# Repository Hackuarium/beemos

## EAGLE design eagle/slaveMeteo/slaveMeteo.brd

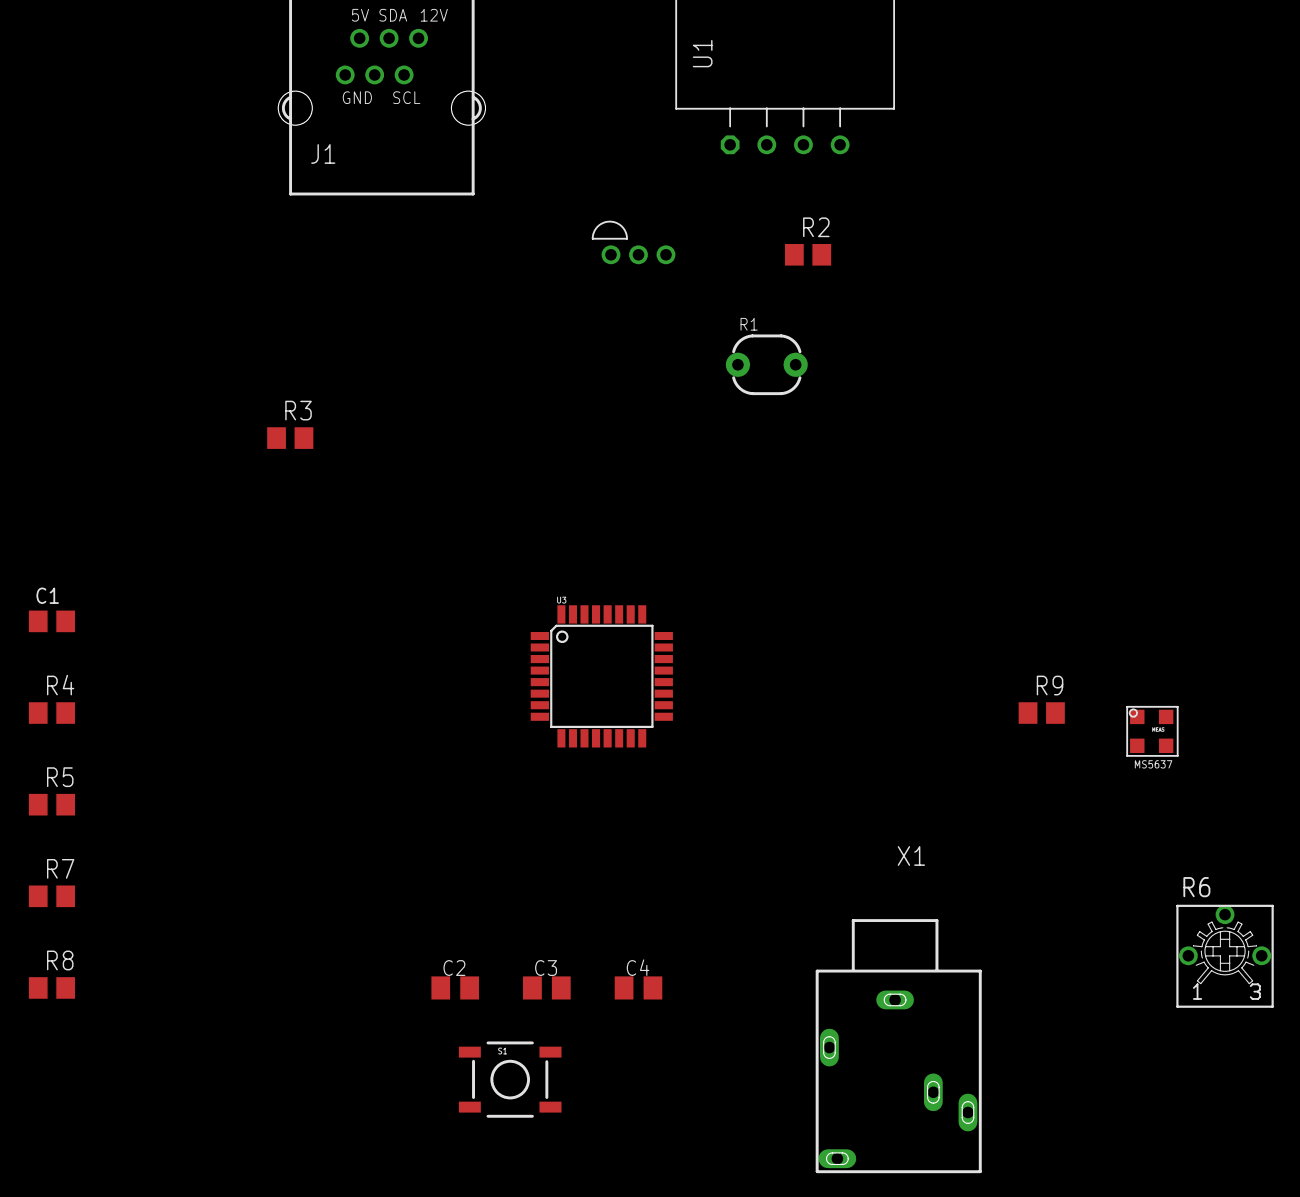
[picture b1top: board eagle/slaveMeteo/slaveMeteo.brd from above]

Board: 2 copper layers, 20 parts (0 on the bottom side), 14 nets, no tracks yet.

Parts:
C1: 100nF; C805
C2, C3, C4: 100nF; C0805K
J1: RJ12RIGHTANGLE-I2C; RJ12-RIGHTANGLE-I2C
R1: PHOTOCELLPTH; PHOTOCELL
R2, R3, R5, R7: R0805
R4, R8: 100k; R0805
R6: 10k; TRIMMER_3362P
R9: 10k; R0805
S1: Reset; TACTILE-SWITCH-SMD-ALT01
U1: RHT03_DHT-22/RA
U3: ATMEGA328; TQFP32-08
U$1: DS1820TO92; DS1820
U$19: MS5637
X1: 1503_09

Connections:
+5V: R1.1, R3.2, R4.2, U1.VDD, U$1.VDD
A0: R3.1, U3.23, U$1.DQ
A1: R1.2, R2.1, U3.24
A2: U1.DATA, U3.25
A6: J1.GND2, U3.19
AREF: C3.1, U3.20
GND: C3.2, C4.2, J1.GND1, R2.2, S1.1, S1.2, U1.GND, U3.3, U3.5, U3.21, U$1.GND, U$19.GND
GND2: R8.1, X1.3
unnamed: C1.1, R4.1, R8.2
unnamed: C1.2, X1.1
RESET: C2.2, R9.1, S1.3, S1.4, U3.29
SCL: J1.SCL, U3.28, U$19.SCL
SDA: J1.SDA, U3.27, U$19.SDA
VCC: C4.1, R9.2, U3.4, U3.6, U3.18, U$19.VDD

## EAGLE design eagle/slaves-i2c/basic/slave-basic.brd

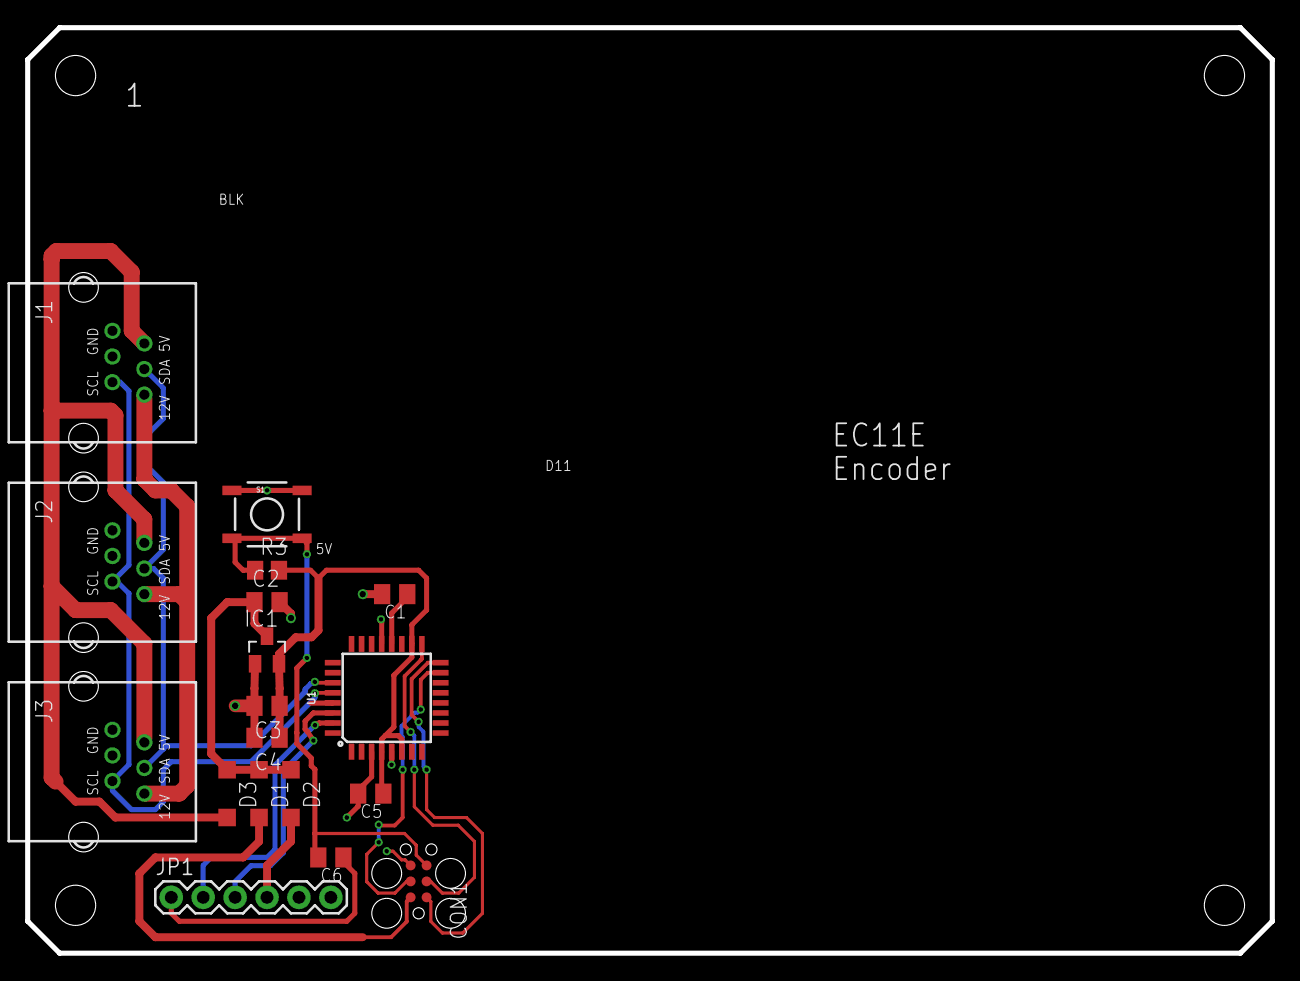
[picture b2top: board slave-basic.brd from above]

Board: 2 copper layers, 99.1 x 73.7 mm, 18 parts (0 on the bottom side), 17 nets.

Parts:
C1, C4, C5, C6: 100nF; C0805K
C2, C3: 10u; C0805K
CON1: SPI; TC2030-MCP
D1, D2, D3: Schottky; SOD123
IC1: MCP1703CB; SOT23
J1, J2, J3: RJ12RIGHTANGLE-I2C; RJ12-RIGHTANGLE-I2C
JP1: FTDI Basic; 1X06
R3: 10k; R0805
S1: Reset; TACTILE-SWITCH-SMD-ALT01
U1: ATMEGA328P_TQFP; TQFP32-08

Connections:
+5V: D3.A, J1.+5V, J2.+5V, J3.+5V
+12V: J1.+12V, J2.+12V, J3.+12V
+XV: C2.1, D1.C, D2.C, D3.C, IC1.3
AREF: C1.1, U1.20
DTR: C6.1, JP1.1
EXT-FTDI: D2.A, JP1.4
EXT-VCC: CON1.5V, D1.A
GND: C1.2, C2.2, C3.2, C4.2, C5.2, CON1.GND, IC1.1, J1.GND1, J1.GND2, J2.GND1, J2.GND2, J3.GND1, J3.GND2, JP1.5, JP1.6, S1.1, S1.2, U1.3, U1.5, U1.21
MISO: CON1.MISO, U1.16
MOSI: CON1.MOSI, U1.15
RESET: C6.2, CON1.RESET, R3.1, S1.3, S1.4, U1.29
RX: JP1.3, U1.30
SCK: CON1.SCK, U1.17
SCL: J1.SCL, J2.SCL, J3.SCL, U1.28
SDA: J1.SDA, J2.SDA, J3.SDA, U1.27
TX: JP1.2, U1.31
VCC: C3.1, C4.1, C5.1, IC1.2, R3.2, U1.4, U1.6, U1.18

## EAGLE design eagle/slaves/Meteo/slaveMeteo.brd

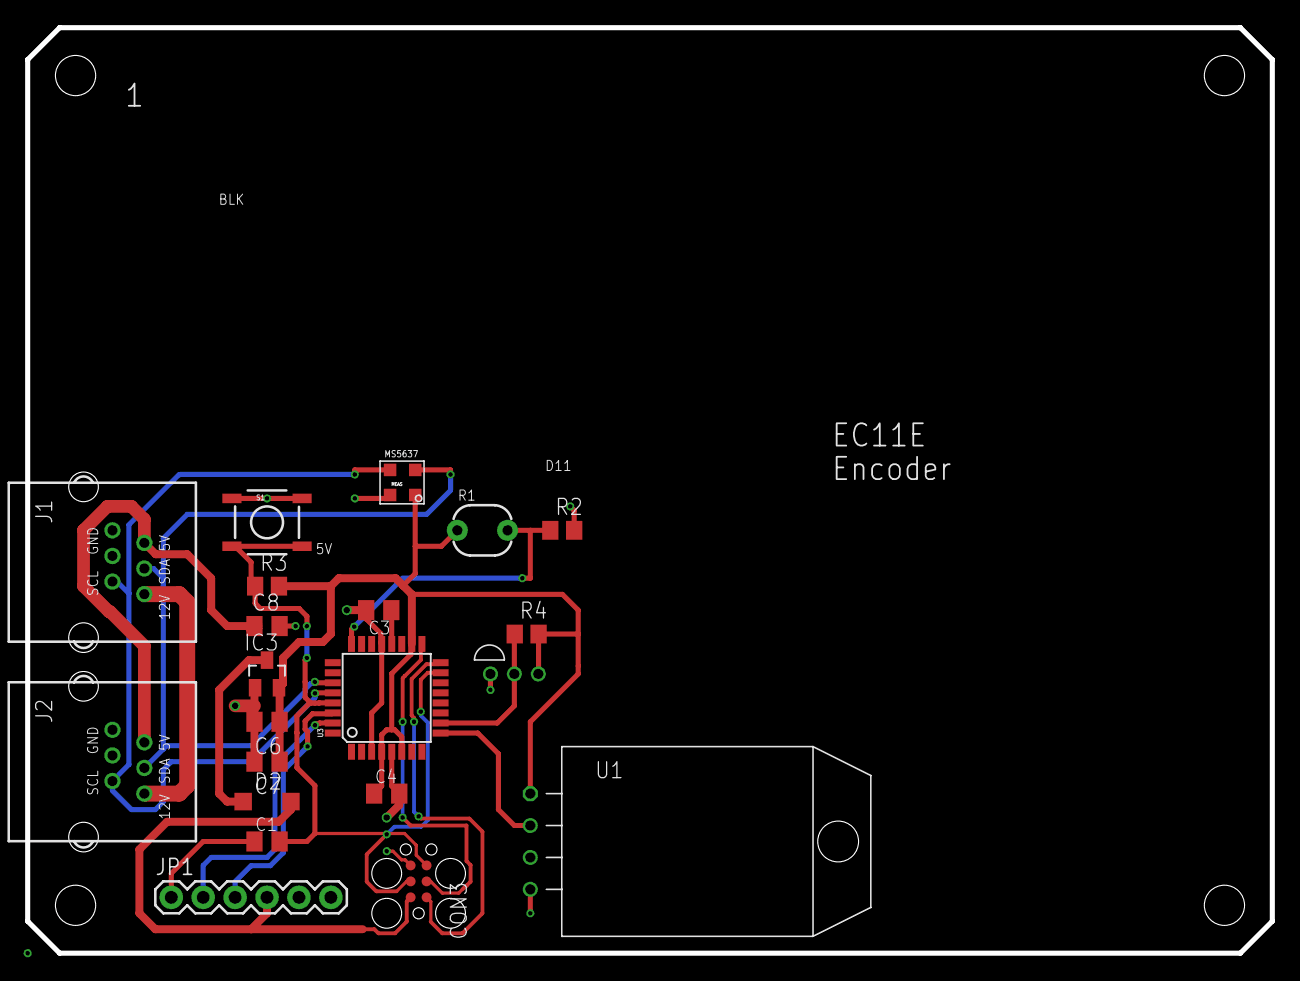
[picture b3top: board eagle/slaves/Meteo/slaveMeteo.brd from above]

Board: 2 copper layers, 99.1 x 73.7 mm, 21 parts (0 on the bottom side), 18 nets.

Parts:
C1, C3, C4, C7: 100nF; C0805K
C6, C8: 10u; C0805K
CON3: SPI; TC2030-MCP
D2: Schottky; SOD123
IC3: MCP1703CB; SOT23
J1, J2: RJ12RIGHTANGLE-I2C; RJ12-RIGHTANGLE-I2C
JP1: FTDI Basic; 1X06
R1: PHOTOCELLPTH; PHOTOCELL
R2, R4: R0805
R3: 10k; R0805
S1: Reset; TACTILE-SWITCH-SMD-ALT01
U1: RHT03_DHT-22/RA
U3: ATMEGA328; TQFP32-08
U$1: DS1820TO92; DS1820
U$19: MS5637

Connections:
+5V: C8.1, D2.C, IC3.3, J1.+5V, J2.+5V
+12V: J1.+12V, J2.+12V
A1: R1.2, R2.1, U3.24
AREF: C3.1, U3.20
D5: U1.DATA, U3.9
D6: R4.1, U3.10, U$1.DQ
DTR: C1.1, JP1.1
EXT-VCC: CON3.5V, D2.A, JP1.4
GND: C3.2, C4.2, C6.2, C7.2, C8.2, CON3.GND, IC3.1, J1.GND1, J1.GND2, J2.GND1, J2.GND2, JP1.5, JP1.6, R2.2, S1.1, S1.2, U1.GND, U3.3, U3.5, U3.21, U$1.GND, U$19.GND
MISO: CON3.MISO, U3.16
MOSI: CON3.MOSI, U3.15
RESET: C1.2, CON3.RESET, R3.1, S1.3, S1.4, U3.29
RX: JP1.3, U3.30
SCK: CON3.SCK, U3.17
SCL: J1.SCL, J2.SCL, U3.28, U$19.SCL
SDA: J1.SDA, J2.SDA, U3.27, U$19.SDA
TX: JP1.2, U3.31
VCC: C4.1, C6.1, C7.1, IC3.2, R1.1, R3.2, R4.2, U1.VDD, U3.4, U3.6, U3.18, U$1.VDD, U$19.VDD

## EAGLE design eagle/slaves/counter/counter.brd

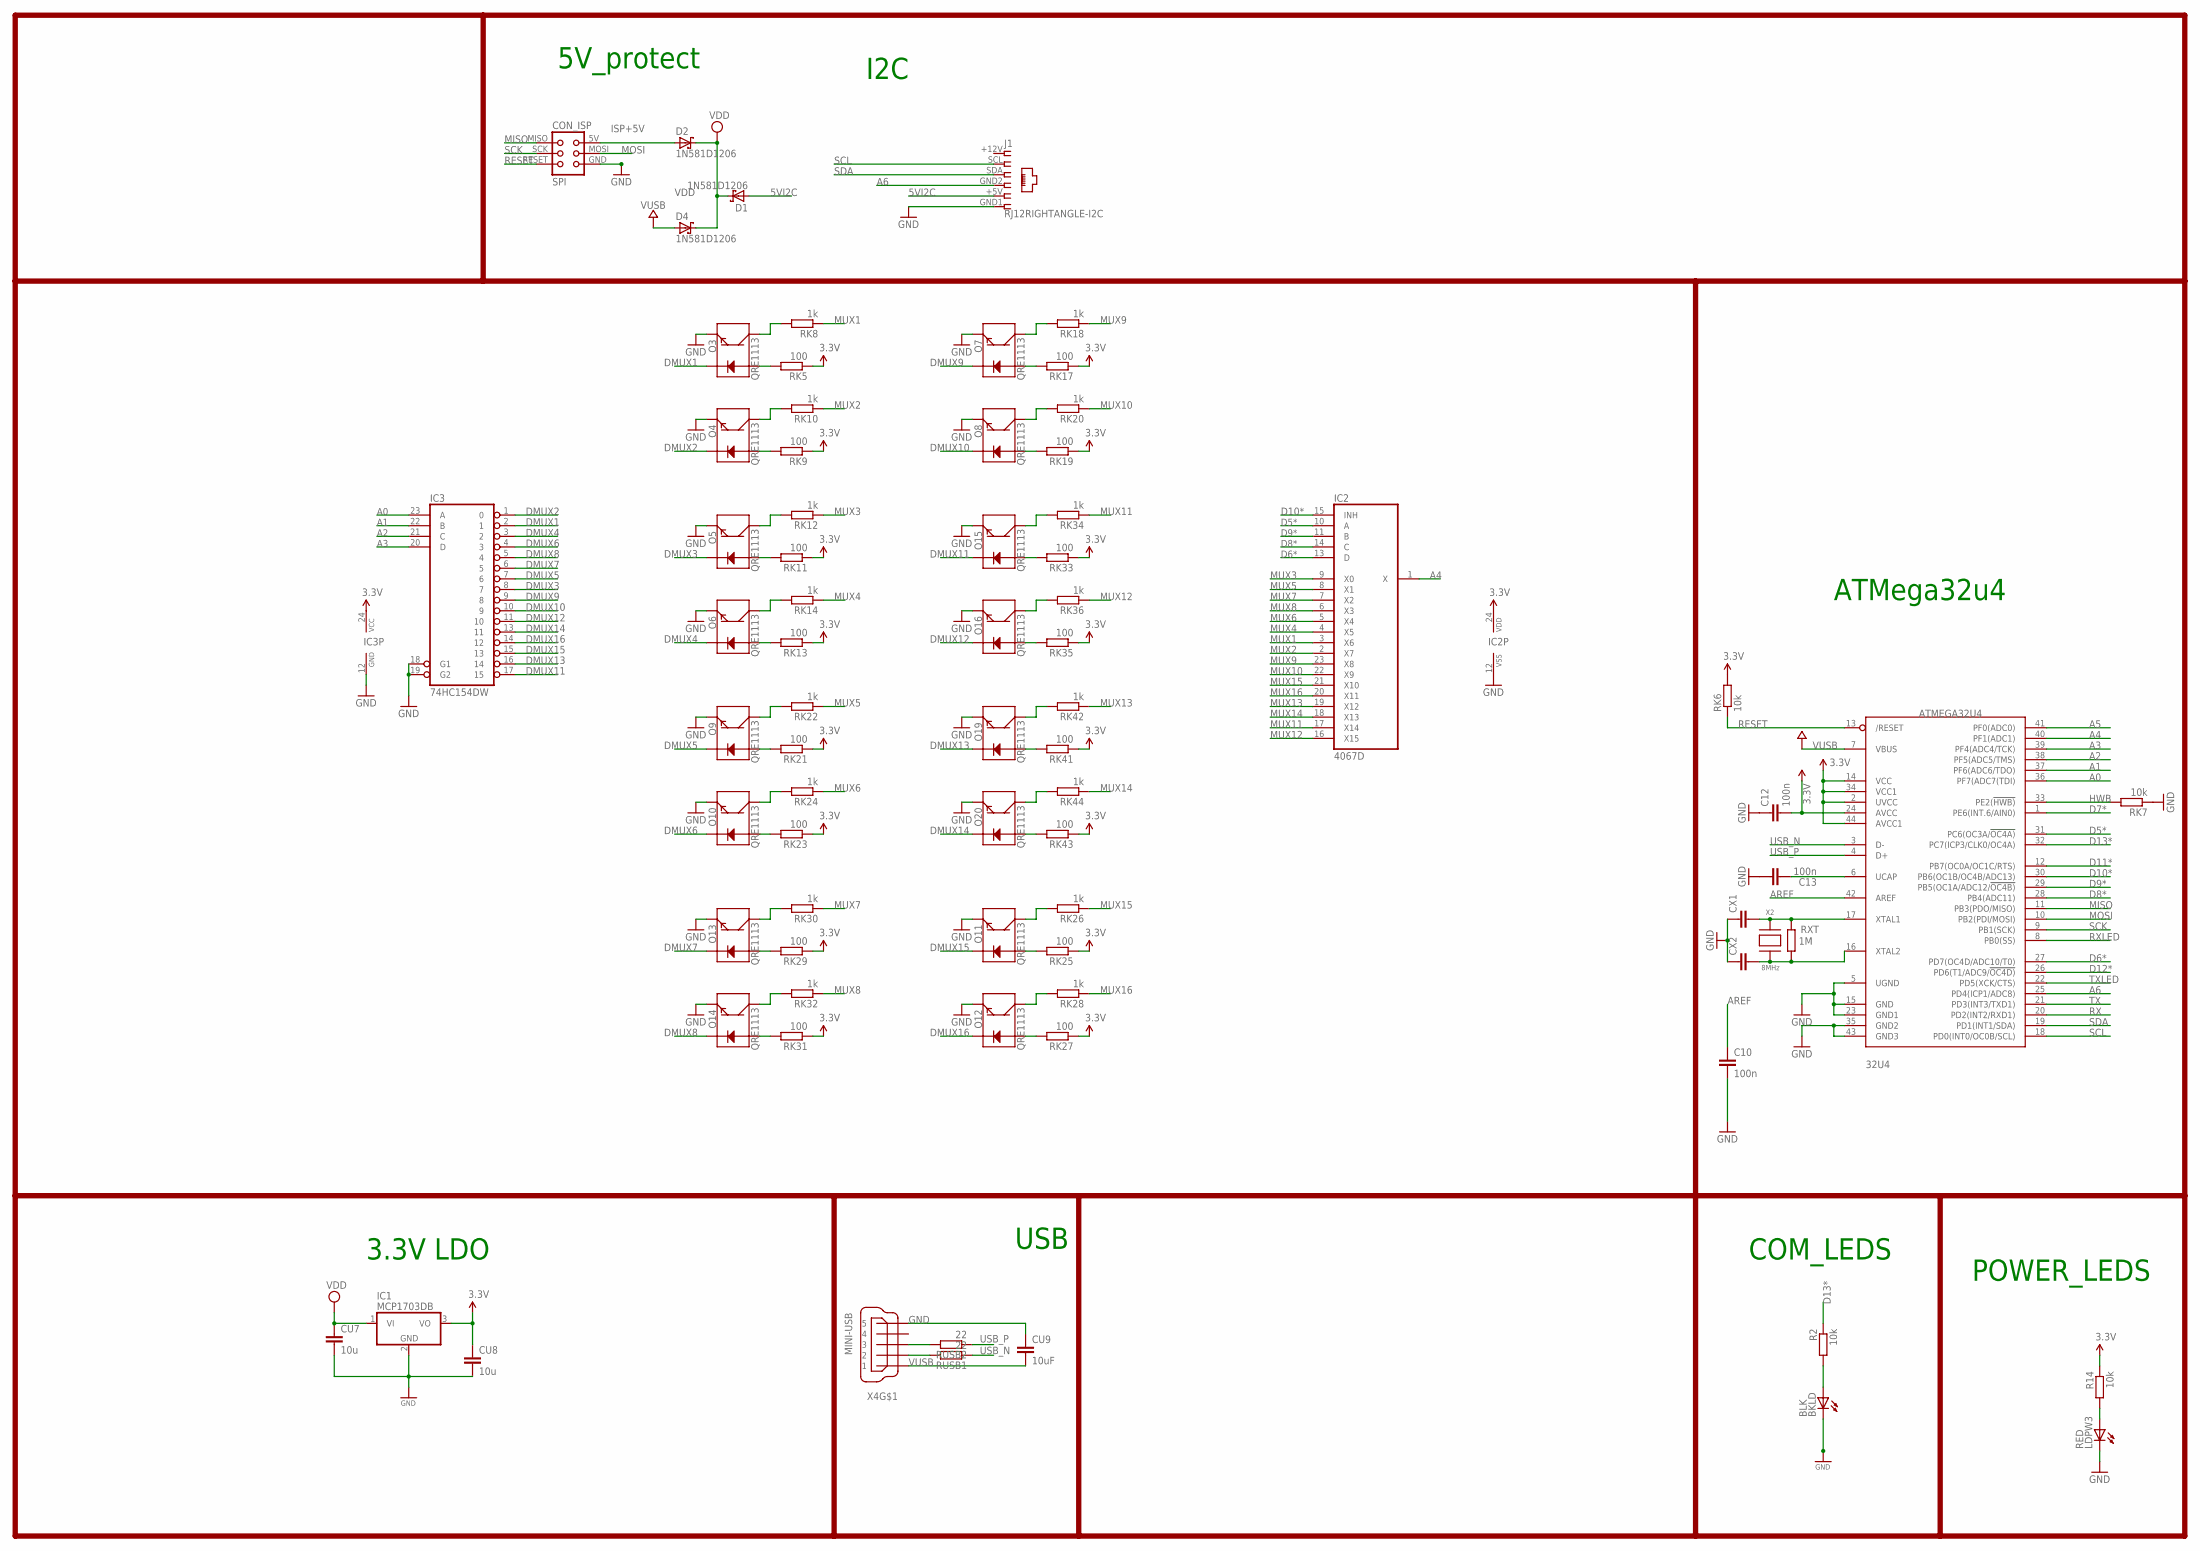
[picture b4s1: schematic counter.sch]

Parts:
32U4: ATMEGA32U4; TQFP44
BKLD: BLK; CHIP-LED0805
C10, C12, C13: 100n; C0805
CON_ISP: SPI; TC2030-MCP-NL
CU7, CU8: 10u; C0805
CU9: 10uF; C0805
CX1, CX2: 22pF; C0805
D1, D2, D4: 1N581D1206; LED-1206
IC1: MCP1703DB; SOT223
IC2: 4067D; SO24W
IC3: 74HC154DW; SO24W
J1: RJ12RIGHTANGLE-I2C; RJ12-RIGHTANGLE-I2C
LDPW3: RED; CHIP-LED0805
O3, O4, O5, O6, O7, O8, O9, O10, O11, O12, O13, O14, O15, O16, O19, O20: QRE1113
R2, R14: 10k; R0805
RK5, RK9, RK11, RK13, RK17, RK19, RK21, RK23, RK25, RK27, RK29, RK31, RK33, RK35, RK41, RK43: 100; M0805
RK6, RK7: 10k; M0805
RK8, RK10, RK12, RK14, RK18, RK20, RK22, RK24, RK26, RK28, RK30, RK32, RK34, RK36, RK42, RK44: 1k; M0805
RUSB1, RUSB2: 22; M0805
RXT: 1M; R0805
X2: 8MHz; NX6035
X4: MINI-USB; 32005-201

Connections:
1: J1.+12V (1)
3.3V: 32U4.2 (UVCC), 32U4.14 (VCC), 32U4.24 (AVCC), 32U4.34 (VCC1), 32U4.44 (AVCC1), C12.2, CU8.1, IC1.3 (VO), IC2.24 (VDD), IC3.24 (VCC), R14.1, RK5.1, RK6.2, RK9.1, RK11.1, RK13.1, RK17.1, RK19.1, RK21.1, RK23.1, RK25.1, RK27.1, RK29.1, RK31.1, RK33.1, RK35.1, RK41.1, RK43.1
5VI2C: D1.A, J1.+5V (5)
A0: 32U4.36 (PF7(ADC7(TDI)), IC3.23 (A)
A1: 32U4.37 (PF6(ADC6/TDO)), IC3.22 (B)
A2: 32U4.38 (PF5(ADC5/TMS)), IC3.21 (C)
A3: 32U4.39 (PF4(ADC4/TCK)), IC3.20 (D)
A4: 32U4.40 (PF1(ADC1)), IC2.1 (X)
A5: 32U4.41 (PF0(ADC0))
A6: 32U4.25 (PD4(ICP1/ADC8)), J1.GND2 (4)
AREF: 32U4.42 (AREF), C10.1
D5*: 32U4.31 (PC6(OC3A/!OC4A)), IC2.10 (A)
D6*: 32U4.27 (PD7(OC4D/ADC10/T0)), IC2.13 (D)
D7*: 32U4.1 (PE6(INT.6/AIN0))
D8*: 32U4.28 (PB4(ADC11)), IC2.14 (C)
D9*: 32U4.29 (PB5(OC1A/ADC12/!OC4B)), IC2.11 (B)
D10*: 32U4.30 (PB6(OC1B/OC4B/ADC13)), IC2.15 (INH)
D11*: 32U4.12 (PB7(OC0A/OC1C/RTS))
D12*: 32U4.26 (PD6(T1/ADC9/!OC4D))
D13*: 32U4.32 (PC7(ICP3/CLK0/OC4A)), R2.1
DMUX1: IC3.2 (1), O3.2 (K)
DMUX2: IC3.1 (0), O4.2 (K)
DMUX3: IC3.8 (7), O5.2 (K)
DMUX4: IC3.3 (2), O6.2 (K)
DMUX5: IC3.7 (6), O9.2 (K)
DMUX6: IC3.4 (3), O10.2 (K)
DMUX7: IC3.6 (5), O13.2 (K)
DMUX8: IC3.5 (4), O14.2 (K)
DMUX9: IC3.9 (8), O7.2 (K)
DMUX10: IC3.10 (9), O8.2 (K)
DMUX11: IC3.17 (15), O15.2 (K)
DMUX12: IC3.11 (10), O16.2 (K)
DMUX13: IC3.16 (14), O19.2 (K)
DMUX14: IC3.13 (11), O20.2 (K)
DMUX15: IC3.15 (13), O11.2 (K)
DMUX16: IC3.14 (12), O12.2 (K)
GND: 32U4.5 (UGND), 32U4.15 (GND), 32U4.23 (GND1), 32U4.35 (GND2), 32U4.43 (GND3), BKLD.C, C10.2, C12.1, C13.1, CON_ISP.GND, CU7.2, CU8.2, CU9.1, CX1.1, CX2.1, IC1.2 (GND), IC2.12 (VSS), IC3.12 (GND), IC3.18 (G1), IC3.19 (G2), J1.GND1 (6), LDPW3.C, O3.4 (E), O4.4 (E), O5.4 (E), O6.4 (E), O7.4 (E), O8.4 (E), O9.4 (E), O10.4 (E), O11.4 (E), O12.4 (E), O13.4 (E), O14.4 (E), O15.4 (E), O16.4 (E), O19.4 (E), O20.4 (E), RK7.1, X4.5
HWB: 32U4.33 (PE2(!HWB)), RK7.2
ISP+5V: CON_ISP.5V (VCC), D2.A
MISO: 32U4.11 (PB3(PDO/MISO)), CON_ISP.MISO
MOSI: 32U4.10 (PB2(PDI/MOSI)), CON_ISP.MOSI
MUX1: IC2.3 (X6), RK8.1
MUX2: IC2.2 (X7), RK10.1
MUX3: IC2.9 (X0), RK12.1
MUX4: IC2.4 (X5), RK14.1
MUX5: IC2.8 (X1), RK22.1
MUX6: IC2.5 (X4), RK24.1
MUX7: IC2.7 (X2), RK30.1
MUX8: IC2.6 (X3), RK32.1
MUX9: IC2.23 (X8), RK18.1
MUX10: IC2.22 (X9), RK20.1
MUX11: IC2.17 (X14), RK34.1
MUX12: IC2.16 (X15), RK36.1
MUX13: IC2.19 (X12), RK42.1
MUX14: IC2.18 (X13), RK44.1
MUX15: IC2.21 (X10), RK26.1
MUX16: IC2.20 (X11), RK28.1
unnamed: 32U4.6 (UCAP), C13.2
unnamed: BKLD.A, R2.2
unnamed: LDPW3.A, R14.2
unnamed: 32U4.17 (XTAL1), CX1.2, RXT.2, X2.P$2
RD3: O3.1 (A), RK5.2
RD4: O4.1 (A), RK9.2
RD5: O5.1 (A), RK11.2
RD6: O6.1 (A), RK13.2
RD7: O7.1 (A), RK17.2
RD8: O8.1 (A), RK19.2
RD9: O9.1 (A), RK21.2
RD10: O10.1 (A), RK23.2
RD11: O11.1 (A), RK25.2
RD12: O12.1 (A), RK27.2
RD13: O13.1 (A), RK29.2
RD14: O14.1 (A), RK31.2
RD15: O15.1 (A), RK33.2
RD16: O16.1 (A), RK35.2
RD19: O19.1 (A), RK41.2
RD20: O20.1 (A), RK43.2
RESET: 32U4.13 (/RESET), CON_ISP.RESET, RK6.1
RX: 32U4.20 (PD2(INT2/RXD1))
RXLED: 32U4.8 (PB0(SS))
SCK: 32U4.9 (PB1(SCK)), CON_ISP.SCK
SCL: 32U4.18 (PD0(INT0/OC0B/SCL)), J1.SCL (2)
SDA: 32U4.19 (PD1(INT1/SDA)), J1.SDA (3)
TX: 32U4.21 (PD3(INT3/TXD1))
TXLED: 32U4.22 (PD5(XCK/CTS))
USBC_N: RUSB1.2, X4.2
USBC_P: RUSB2.2, X4.3
USB_N: 32U4.3 (D-), RUSB1.1
USB_P: 32U4.4 (D+), RUSB2.1
VDD: CU7.1, D1.C, D2.C, D4.C, IC1.1 (VI)
VUSB: 32U4.7 (VBUS), CU9.2, D4.A, X4.1
XTAL1: 32U4.16 (XTAL2), CX2.2, RXT.1, X2.P$1
Y3: O3.3 (C), RK8.2
Y4: O4.3 (C), RK10.2
Y5: O5.3 (C), RK12.2
Y6: O6.3 (C), RK14.2
Y7: O7.3 (C), RK18.2
Y8: O8.3 (C), RK20.2
Y9: O9.3 (C), RK22.2
Y10: O10.3 (C), RK24.2
Y11: O11.3 (C), RK26.2
Y12: O12.3 (C), RK28.2
Y13: O13.3 (C), RK30.2
Y14: O14.3 (C), RK32.2
Y15: O15.3 (C), RK34.2
Y16: O16.3 (C), RK36.2
Y19: O19.3 (C), RK42.2
Y20: O20.3 (C), RK44.2

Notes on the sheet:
USB
I2C
5V_protect
POWER_LEDS
COM_LEDS
3.3V LDO
ATMega32u4

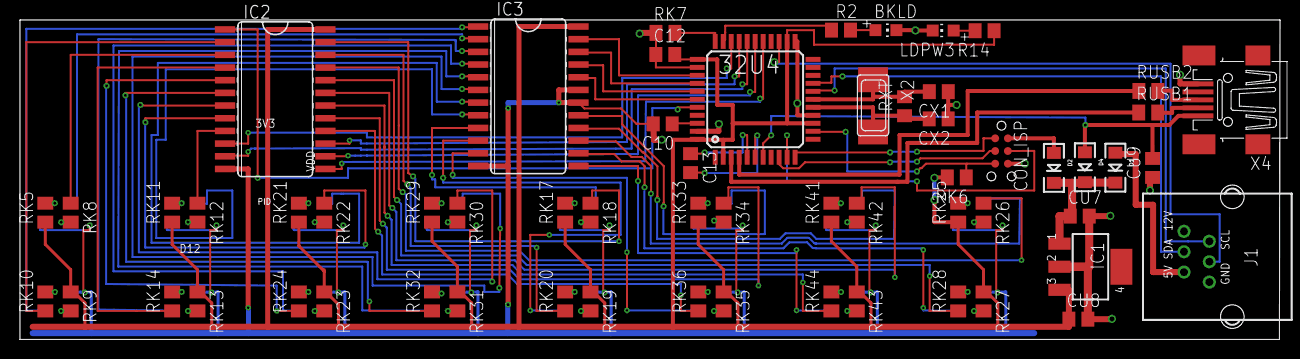
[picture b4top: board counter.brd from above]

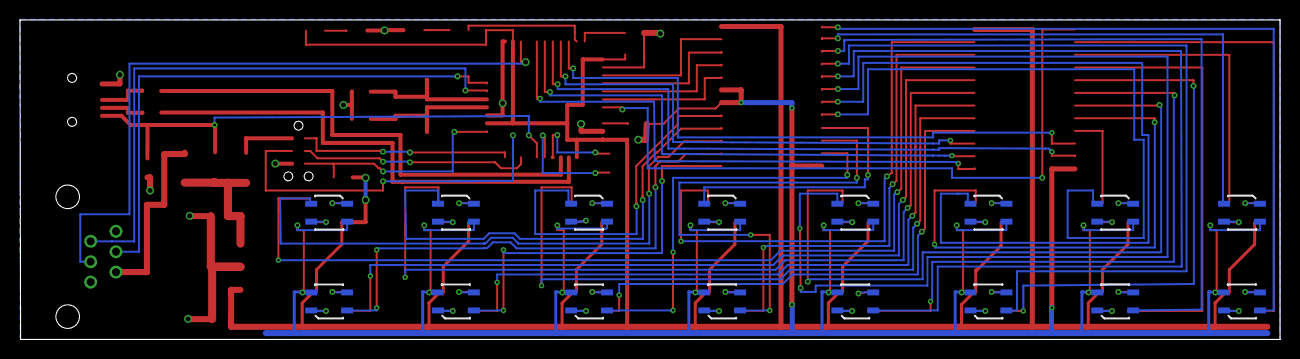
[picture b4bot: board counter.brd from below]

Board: 4 copper layers, 126.2 x 32.0 mm, 76 parts (16 on the bottom side), 99 nets.

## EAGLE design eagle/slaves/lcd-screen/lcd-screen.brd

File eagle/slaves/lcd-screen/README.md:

# LCD 16x2 slave
# ATmega328 pin map

| Pin    | Map to        | Function | Remarks
| ------ | ------------- | -------- | -------
| D0     | PD0(RXD)      | RX       |
| D1     | PD1(TXD)      | TX       |
| D2     | PD2(INT0)     | Rot A    | Interrupt allows wake up
| D3     | PD3(INT1)     | Rot Int  | Interrupt allows wake up
| D4     | PD4(XCK/T0)   | Rot B    |
| D5     | PD5(T1)       | LCD E    | Counter
| D6     | PD6(AIN0)     | LCD DB4  |
| D7     | PD7(AIN1)     | LCD DB5  |
| D8     | PB0(ICP)      | LCD DB6  |
| D9     | PB1(OC1A)     | LCD DB7  | PWM
| D10    | PB2(SS/OC1B)  | LCD A    | PWM
| D11    | PB3(MOSI/OC2) | MOSI     |
| D12    | PB4(MISO)     | MISO     |
| D13    | PB5(SCK)      | SCK      |
| D14 A0 | PC0(ADC0)     | LCD VDD  | ADC
| D15 A1 | PC1(ADC1)     |          | ADC
| D16 A2 | PC2/ADC2)     |          | ADC
| D17 A3 | PC3(ADC3)     |          | ADC
| D18 A4 | PC4(ADC4/SDA) | SDA      |
| D19 A5 | PC5(ADC5/SCL) | SCL      |
w

Remarks
* RX, TX used for serial communication over USB (debug)
* SDA, SCL: I2C communication with master
* MOSI, MISO, SCK: boot loader

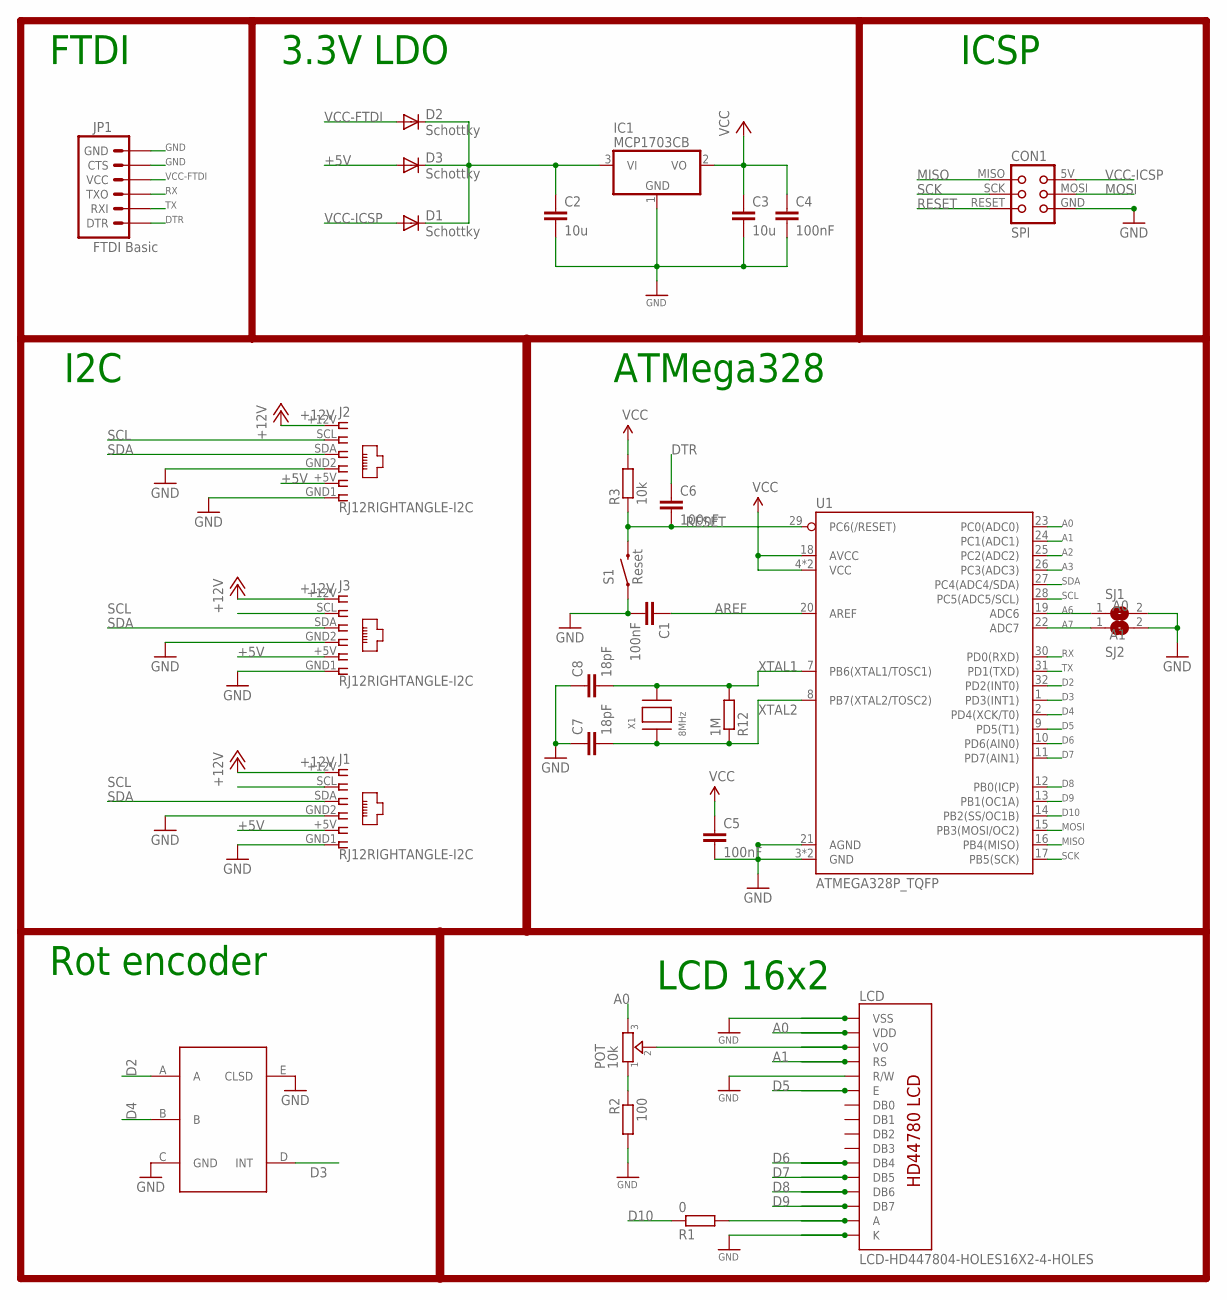
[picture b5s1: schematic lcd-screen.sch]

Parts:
C1, C4, C5, C6: 100nF; C0805K; MPN 80-C1206C104K5R; LCSC C49678
C2, C3: 10u; C0805K; MPN 77-VJ1206V106ZXQTBC; LCSC C15850
C7, C8: 18pF; C0805K; MPN 77-VJ1206A180JXXPBC; LCSC C1797
CON1: SPI; TC2030-MCP
D1, D2, D3: Schottky; SOD123; MPN 621-1N5819HW-F; LCSC C82544
IC1: MCP1703CB; SOT23; LCSC C53352
J1, J2, J3: RJ12RIGHTANGLE-I2C; RJ12-RIGHTANGLE-I2C
JP1: FTDI Basic; 1X06
LCD: LCD-HD447804-HOLES16X2-4-HOLES; LCD-16X2-4HOLES
POT: 10k; TRIMMER_3362P
R1: 0; R0805; LCSC C17477
R2: 100; R0805; LCSC C17408
R3: 10k; R0805; LCSC C17513
R12: 1M; R0805; LCSC C17514
S1: Reset; TACTILE-SWITCH-SMD-ALT01
SJ1: A0; SJ
SJ2: A1; SJ
U1: ATMEGA328P_TQFP; TQFP32-08
U$1: EC11E
X1: 8MHz; NX6035; MPN 729-F60800010; LCSC C122522

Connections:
+5V: D3.A, J1.+5V (5), J2.+5V (5), J3.+5V (5)
+12V: J1.+12V (1), J2.+12V (1), J3.+12V (1)
+XV: C2.1, D1.C, D2.C, D3.C, IC1.3 (VI)
A0: LCD.2 (VDD), POT.3, U1.23 (PC0(ADC0))
A1: LCD.4 (RS), U1.24 (PC1(ADC1))
A2: U1.25 (PC2(ADC2))
A3: U1.26 (PC3(ADC3))
A6: SJ1.1, U1.19 (ADC6)
A7: SJ2.1, U1.22 (ADC7)
AREF: C1.1, U1.20 (AREF)
D2: U1.32 (PD2(INT0)), U$1.A
D3: U1.1 (PD3(INT1)), U$1.D (INT)
D4: U1.2 (PD4(XCK/T0)), U$1.B
D5: LCD.6 (E), U1.9 (PD5(T1))
D6: LCD.11 (DB4), U1.10 (PD6(AIN0))
D7: LCD.12 (DB5), U1.11 (PD7(AIN1))
D8: LCD.13 (DB6), U1.12 (PB0(ICP))
D9: LCD.14 (DB7), U1.13 (PB1(OC1A))
D10: R1.1, U1.14 (PB2(SS/OC1B))
DTR: C6.1, JP1.1 (DTR)
GND: C1.2, C2.2, C3.2, C4.2, C5.2, C7.1, C8.1, CON1.GND, IC1.1 (GND), J1.GND1 (6), J1.GND2 (4), J2.GND1 (6), J2.GND2 (4), J3.GND1 (6), J3.GND2 (4), JP1.5 (CTS), JP1.6 (GND), LCD.1 (VSS), LCD.5 (R/W), LCD.16 (K), R2.2, S1.1, S1.2 (1), SJ1.2, SJ2.2, U1.3 (GND), U1.5 (GND), U1.21 (AGND), U$1.C (GND), U$1.E (CLSD)
MISO: CON1.MISO, U1.16 (PB4(MISO))
MOSI: CON1.MOSI, U1.15 (PB3(MOSI/OC2))
unnamed: LCD.3 (VO), POT.2
unnamed: POT.1, R2.1
unnamed: LCD.15 (A), R1.2
RESET: C6.2, CON1.RESET, R3.1, S1.3 (2), S1.4 (2), U1.29 (PC6(/RESET))
RX: JP1.3 (TXO), U1.30 (PD0(RXD))
SCK: CON1.SCK, U1.17 (PB5(SCK))
SCL: J1.SCL (2), J2.SCL (2), J3.SCL (2), U1.28 (PC5(ADC5/SCL))
SDA: J1.SDA (3), J2.SDA (3), J3.SDA (3), U1.27 (PC4(ADC4/SDA))
TX: JP1.2 (RXI), U1.31 (PD1(TXD))
VCC: C3.1, C4.1, C5.1, IC1.2 (VO), R3.2, U1.4 (VCC), U1.6 (VCC), U1.18 (AVCC)
VCC-FTDI: D2.A, JP1.4 (VCC)
VCC-ICSP: CON1.5V (VCC), D1.A
XTAL1: C8.2, R12.2, U1.7 (PB6(XTAL1/TOSC1)), X1.P$2
XTAL2: C7.2, R12.1, U1.8 (PB7(XTAL2/TOSC2)), X1.P$1

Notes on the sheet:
ICSP
ATMega328
3.3V LDO
I2C
FTDI
LCD 16x2
Rot encoder

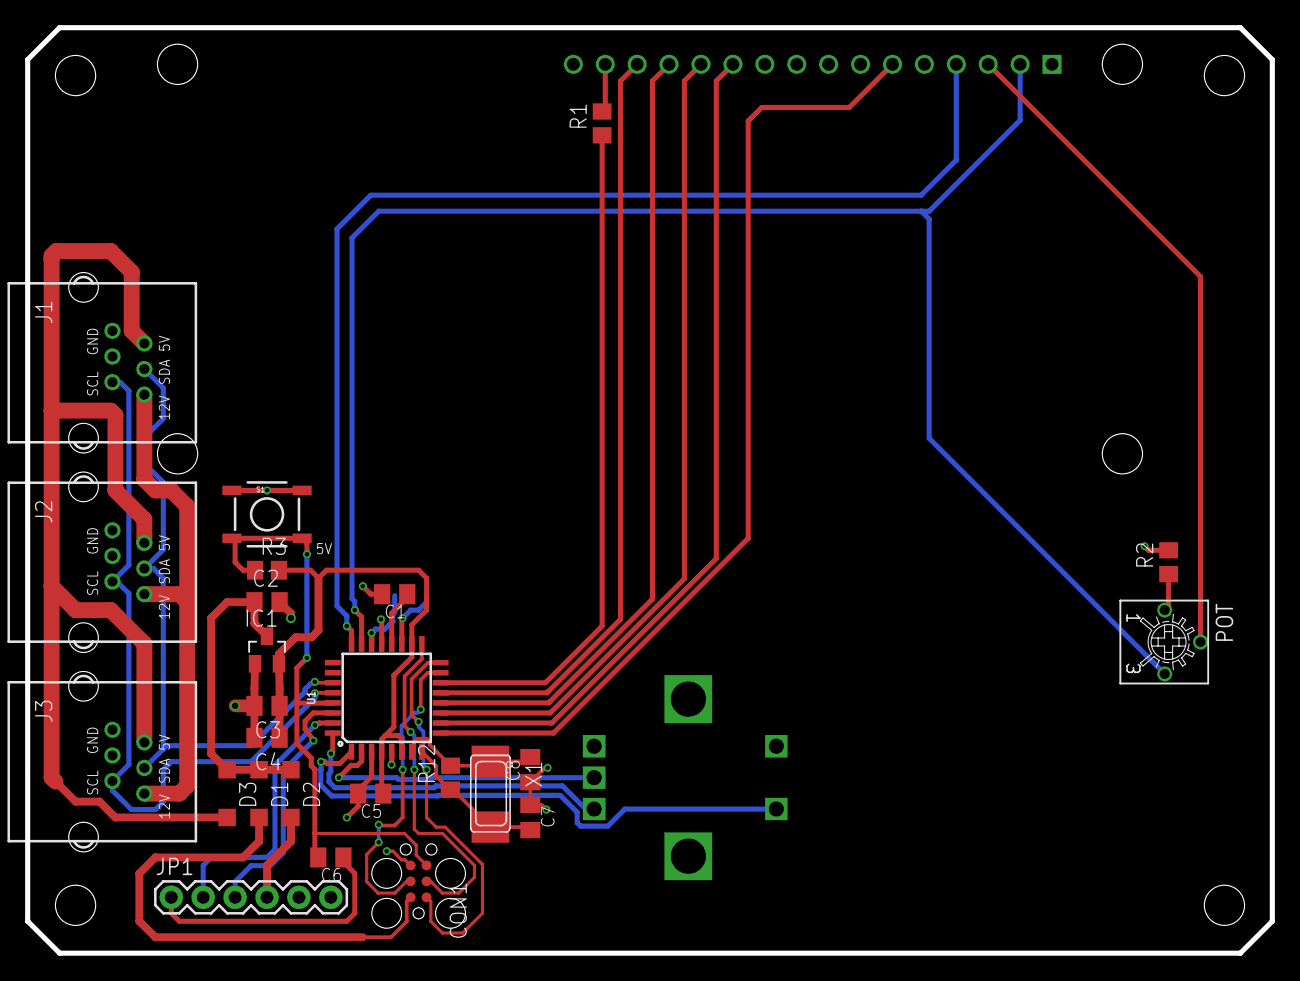
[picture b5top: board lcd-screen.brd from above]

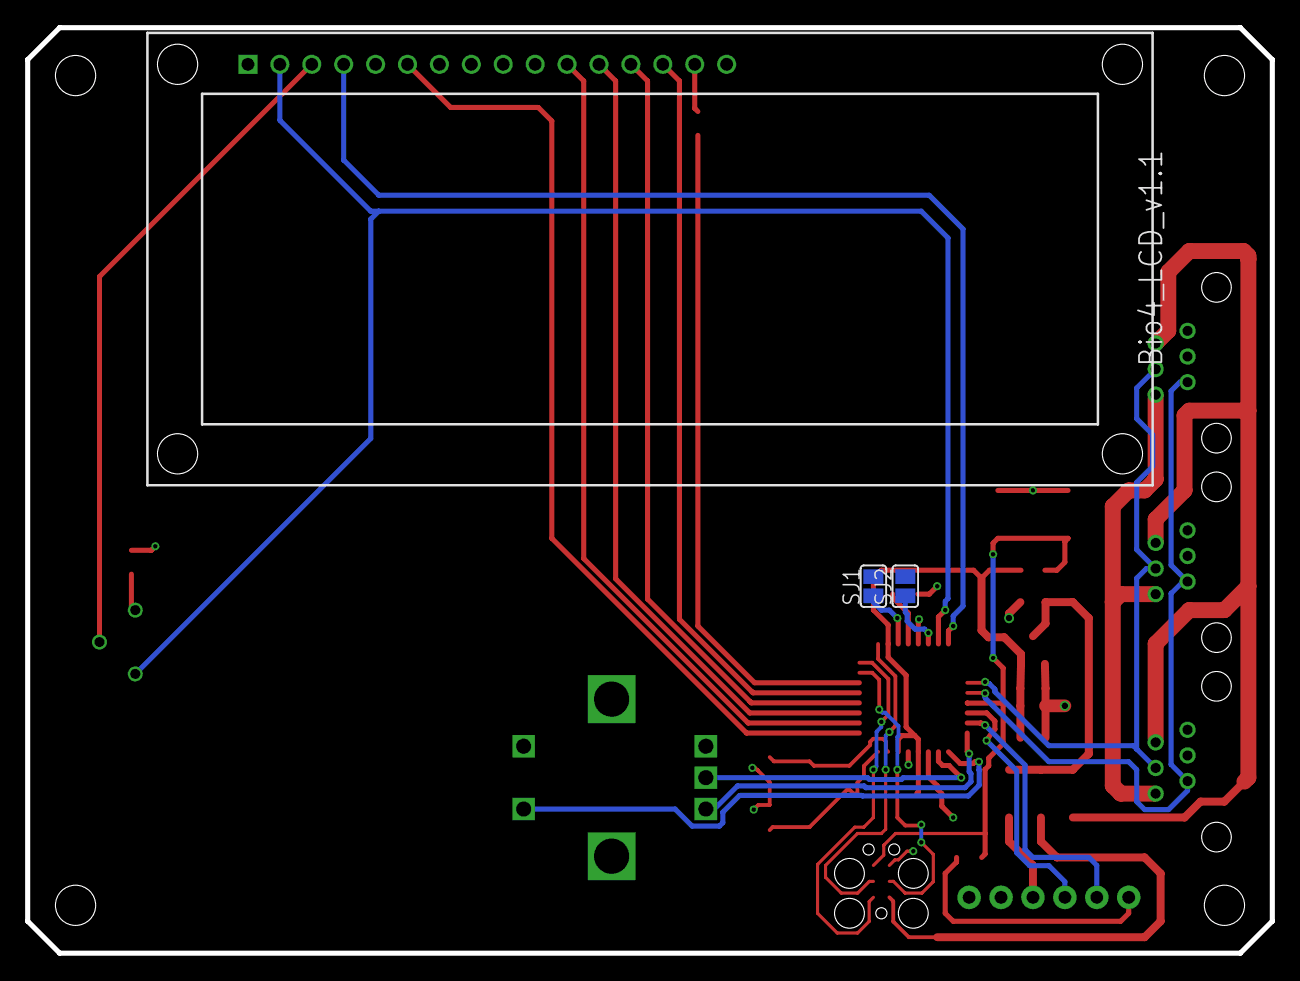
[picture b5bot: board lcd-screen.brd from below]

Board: 2 copper layers, 99.1 x 73.7 mm, 29 parts (4 on the bottom side), 35 nets.

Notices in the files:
parts and their libraries:
lpatiny: ©2009 ROFA.cz - modified and updated by Robert Darlington ‹rdarlington@gmail.com›
SparkFun: Licensing: CC v3.0 Share-Alike You are welcome to use this library for commercial purposes.
